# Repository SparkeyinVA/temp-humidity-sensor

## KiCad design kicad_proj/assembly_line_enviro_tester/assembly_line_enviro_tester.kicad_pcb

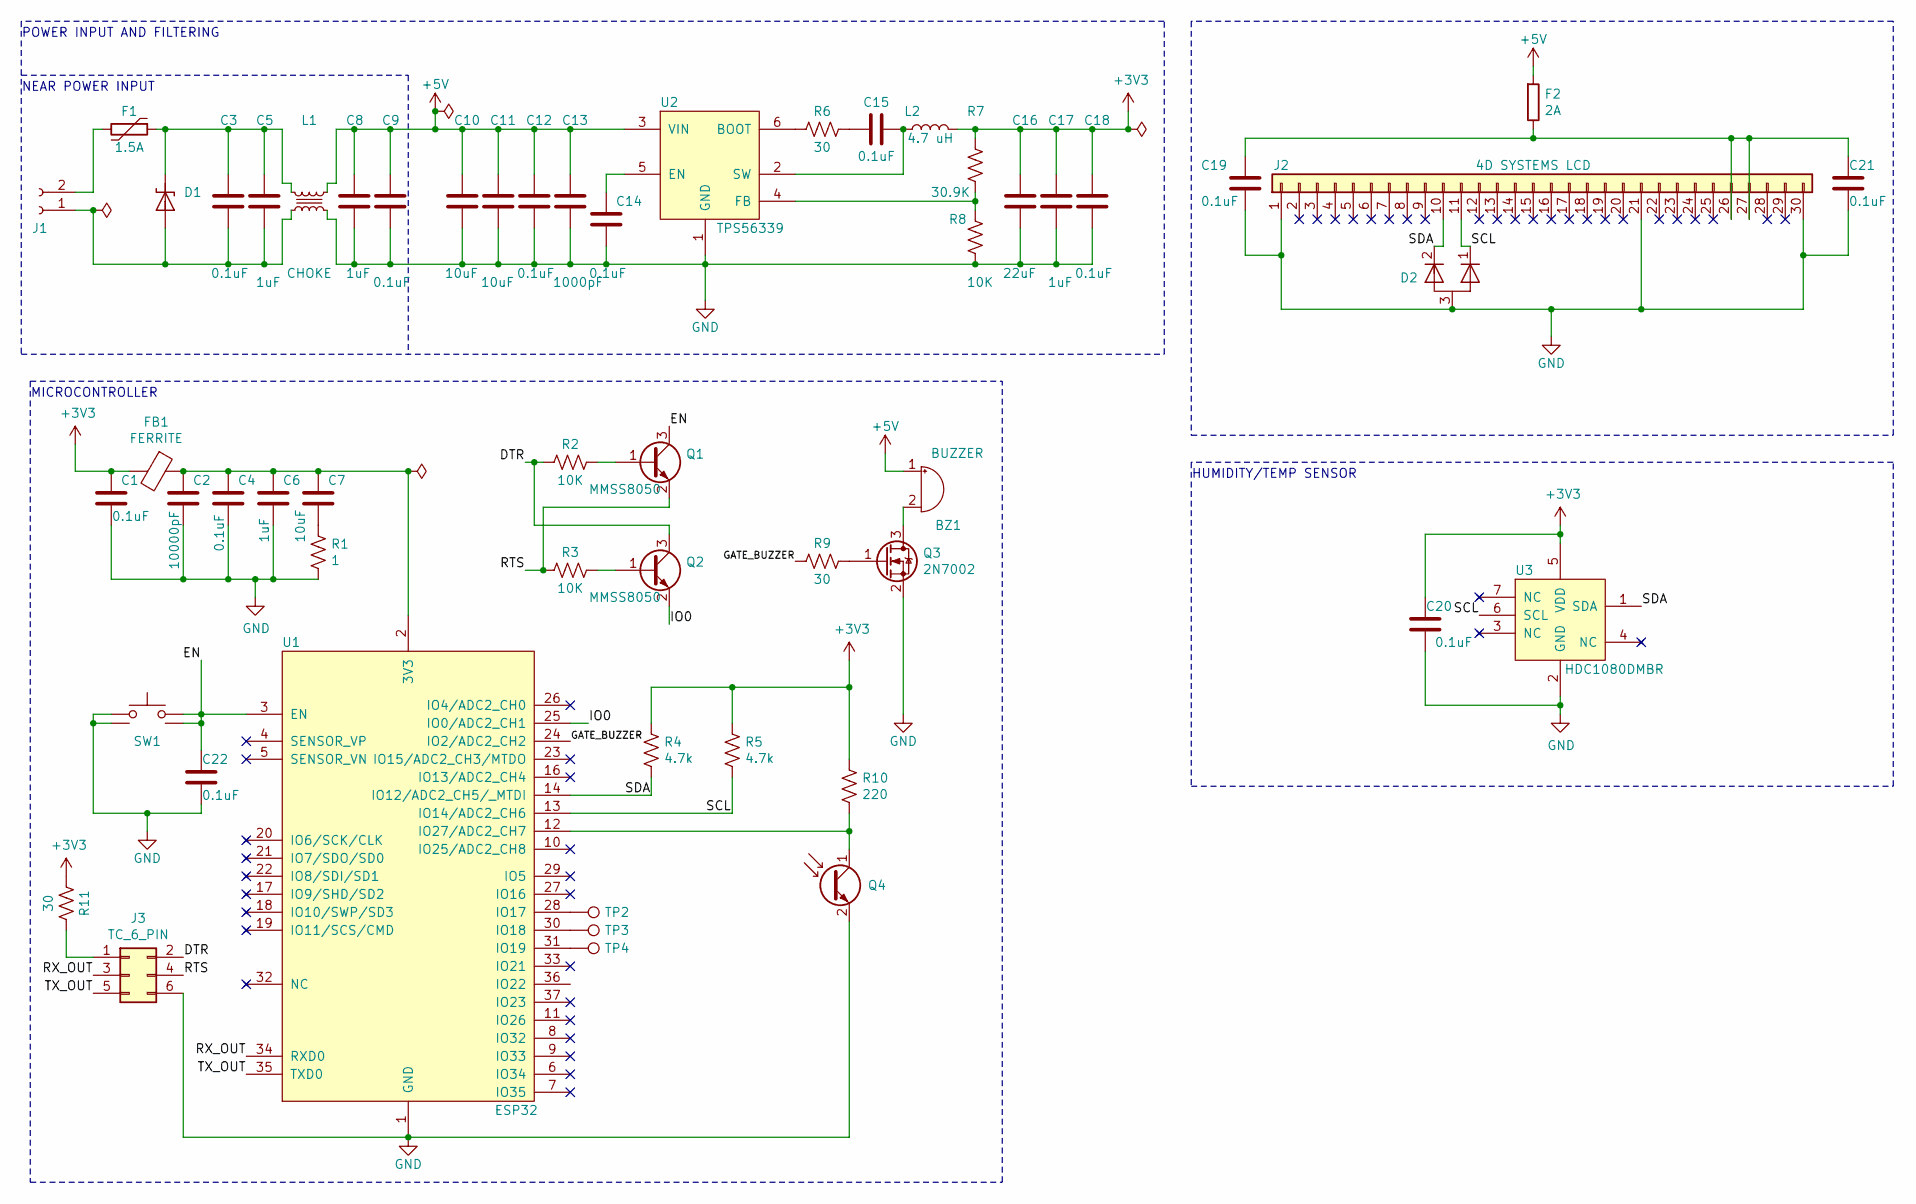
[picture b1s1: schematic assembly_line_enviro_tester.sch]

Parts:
BZ1: SMI-1324-TW-5V-3-R
C1, C3, C4, C9, C12, C14, C15, C18, C19, C20, C21, C22: CC0603KRX7R9BB104; C_0603_1608Metric
C2: CL10B103KB8NNNC; C_0603_1608Metric
C5, C6, C8, C17: CC0603KRX5R9BB105; C_0603_1608Metric
C7, C10, C11: CL31A106KPHNNNE; C_1206_3216Metric
C13: CL10B102KB8WPNC; C_0603_1608Metric
C16: C2012X7S1A226M125AC; C_0805_2012Metric
D1: P6SMB6.8A-E3_5B; P6SMB6.8A-E3_5BN
D2: RCLAMP0582BQTCT; RCLAMP0582BQTCTN
F1: 0ZCG0150BF2C; Fuse_1812_4532Metric_Castellated
F2: 0686F2000-01; Fuse_0603_1608Metric
FB1: 742792040; L_0805_2012Metric
J1: Conn_01x02_Female; PinSocket_2x01_P2.54mm_Vertical_SMD
J2: 0524353071
J3: Tag_Connect_6_Pin; TC2030_SMALL
L1: ACM4520V-142-2P-T00
L2: CIGW252010EH4R7MNE; CHIP_1008N
Q1, Q2: MMSS8050-L-TP; MMSS8050-L-TPN
Q3: 2N7002-TP
Q4: INL-5APT30; PinSocket_1x02_P2.54mm_Vertical
R1: SR732BTTD1R00D; R_1206_3216Metric
R2, R3, R8: RC0603JR-0710KL; R_0603_1608Metric
R4, R5: RC0603JR-074K7L; R_0603_1608Metric
R6, R9, R11: RC0603JR-0730RL; R_0603_1608Metric
R7: RC0603FR-0730K9L; R_0603_1608Metric
R10: RC0603JR-07220RL; R_0603_1608Metric
SW1: PTS_647_SN70_SMTR2_LFS
TP2, TP3, TP4: TestPoint; TestPoint_Plated_Hole_D2.0mm
U1: ESP32-WROOM-32D
U2: TPS56339DDCR; TPS56339DDCRN
U3: HDC1080DMBR; HDC1080DMBRN

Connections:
+3V3: C1.1, C16.1, C17.1, C18.1, C20.1, FB1.2, L2.2, R4.1, R5.1, R7.1, R10.1, R11.2, U3.5 (VDD)
+5V: BZ1.1 (-), C8.1, C9.1, C10.1, C11.1, C12.1, C13.1, F2.1, L1.1, U2.3 (VIN)
/DTR: J3.2, Q2.3 (C), R2.2
/EN: C22.1, Q1.3 (C), SW1.3, SW1.4, U1.3 (EN)
/GATE_BUZZER: R9.2, U1.24 (IO2/ADC2_CH2)
/IO0: Q2.2 (E), U1.25 (IO0/ADC2_CH1)
/RTS: J3.4, Q1.2 (E), R3.2
/RX_OUT: J3.3, U1.34 (RXD0)
/SCL: D2.1 (A1), J2.11, R5.2, U1.13 (IO14/ADC2_CH6), U3.6 (SCL)
/SDA: D2.2 (A2), J2.10, R4.2, U1.14 (IO12/ADC2_CH5/_MTDI), U3.1 (SDA)
/TX_OUT: J3.5, U1.35 (TXD0)
GND: C1.2, C2.2, C4.2, C6.2, C8.2, C9.2, C10.2, C11.2, C12.2, C13.2, C14.2, C16.2, C17.2, C18.2, C19.2, C20.2, C21.2, C22.2, D2.3 (K), J2.1, J2.21, J2.30, J3.6, L1.2, Q3.2 (S), Q4.2 (E), R1.2, R8.2, SW1.1, SW1.2, U1.1 (GND), U1.15 (GND), U1.38 (GND), U1.39 (GND), U2.1 (GND), U3.2 (GND)
unnamed: BZ1.2 (+), Q3.3 (D)
unnamed: C2.1, C4.1, C6.1, C7.1, FB1.1, U1.2 (3V3)
unnamed: C3.1, C5.1, D1.C, F1.1, L1.4
unnamed: C3.2, C5.2, D1.A, J1.1, L1.3
unnamed: C7.2, R1.1
unnamed: C14.1, U2.5 (EN)
unnamed: C15.1, L2.1, U2.2 (SW)
unnamed: C15.2, R6.1
unnamed: C19.1, C21.1, F2.2, J2.26, J2.27
unnamed: F1.2, J1.2
unnamed: J3.1, R11.1
unnamed: Q1.1 (B), R2.1
unnamed: Q2.1 (B), R3.1
unnamed: Q3.1 (G), R9.1
unnamed: Q4.1 (C), R10.2, U1.12 (IO27/ADC2_CH7)
unnamed: R6.2, U2.6 (BOOT)
unnamed: R7.2, R8.1, U2.4 (FB)
unnamed: TP2.1, U1.28 (IO17)
unnamed: TP3.1, U1.30 (IO18)
unnamed: TP4.1, U1.31 (IO19)

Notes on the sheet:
POWER INPUT AND FILTERING
NEAR POWER INPUT
HUMIDITY/TEMP SENSOR
MICROCONTROLLER

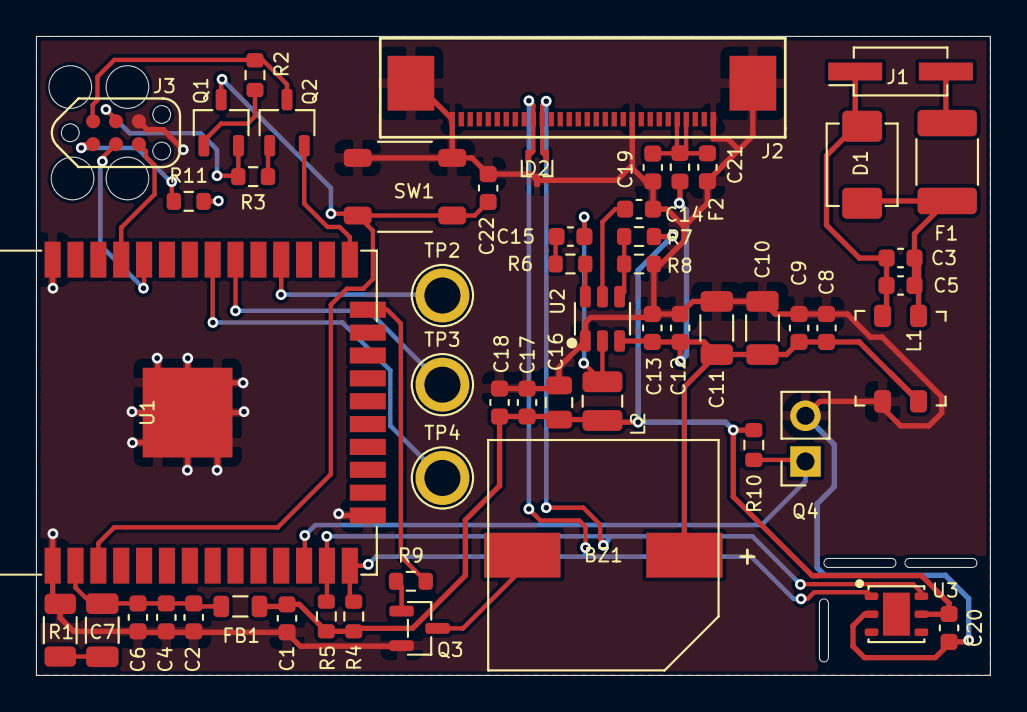
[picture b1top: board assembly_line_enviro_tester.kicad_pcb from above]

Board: 4 copper layers, 53.0 x 35.5 mm, 55 parts (0 on the bottom side), 32 nets.

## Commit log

2021-02-08 Layout as done on YT stream
2021-03-19 first layout try
